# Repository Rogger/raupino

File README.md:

Raupino
=======
Raupino, an Arduino clone for DIY hobbiest

Detailed description: http://michaelrogger.wordpress.com/2014/03/23/raupino-an-arduino-clone/

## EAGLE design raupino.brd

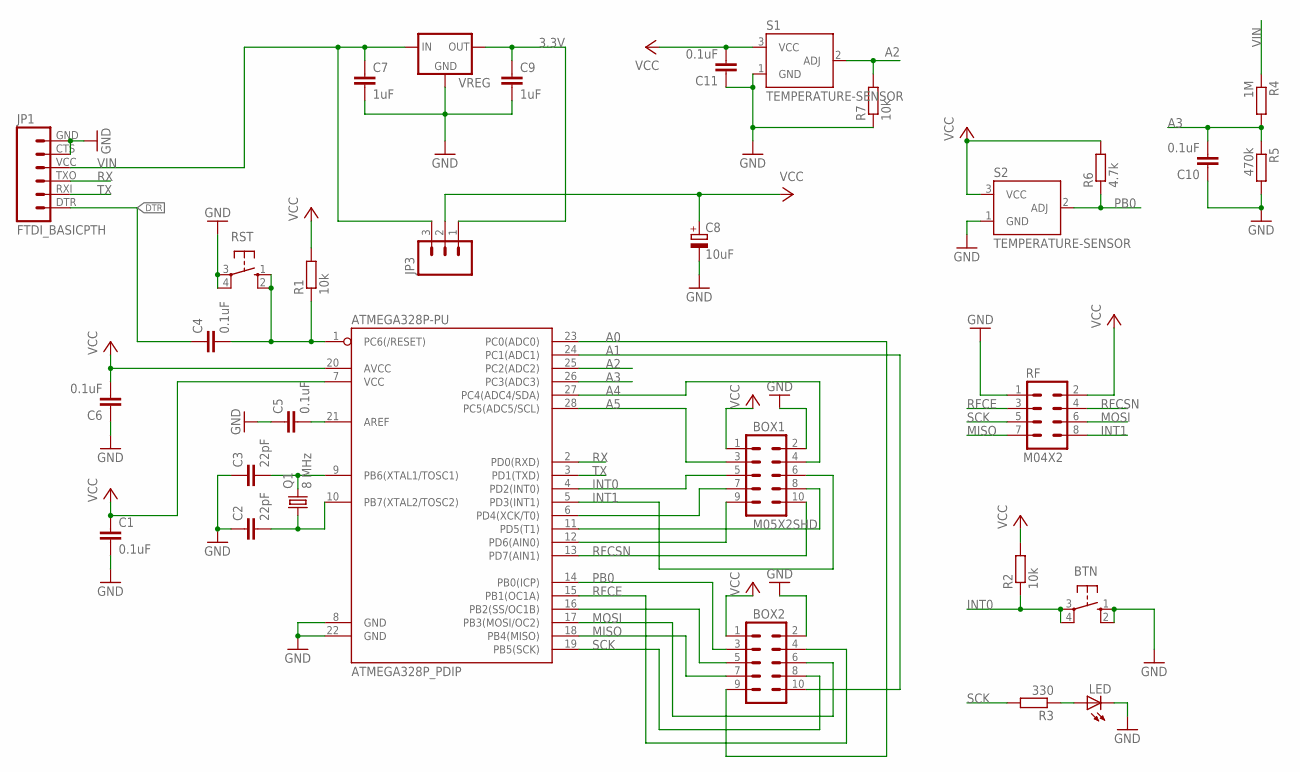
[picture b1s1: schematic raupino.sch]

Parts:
ATMEGA328P-PU: ATMEGA328P_PDIP; DIL28-3
BOX1, BOX2: M05X2SHD; 2X5-SHROUDED
BTN: 10-XX; B3F-10XX
C1, C4, C5, C6, C10, C11: 0.1uF; C0805
C2, C3: 22pF; C0805
C7, C9: 1uF; C050-025X075
C8: 10uF; TT2D5L
JP1: FTDI_BASICPTH; FTDI_BASIC
JP3: M03PTH; 1X03
LED: LED3MM
Q1: 8 MHz; HC49US
R1, R2, R7: 10k; R0805
R3: 330; R0805
R4: 1M; R0805
R5: 470k; R0805
R6: 4.7k; R0805
RF: M04X2; 2X4
RST: 10-XX; B3F-10XX
S1, S2: TEMPERATURE-SENSOR; TO-92
VREG: 78LXX

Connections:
3.3V: C9.1, JP3.1, VREG.OUT
A0: ATMEGA328P-PU.23 (PC0(ADC0)), BOX2.9
A1: ATMEGA328P-PU.24 (PC1(ADC1)), BOX2.10
A2: ATMEGA328P-PU.25 (PC2(ADC2)), R7.2, S1.2 (ADJ)
A3: ATMEGA328P-PU.26 (PC3(ADC3)), C10.2, R4.2, R5.1
A4: ATMEGA328P-PU.27 (PC4(ADC4/SDA)), BOX1.4
A5: ATMEGA328P-PU.28 (PC5(ADC5/SCL)), BOX1.3
DTR: C4.1, JP1.DTR (1)
GND: ATMEGA328P-PU.8 (GND), ATMEGA328P-PU.22 (GND), BOX1.2, BOX2.2, BTN.1 (S), BTN.2 (S1), C1.2, C2.1, C3.1, C5.1, C6.1, C7.2, C8.-, C9.2, C10.1, C11.1, JP1.CTS (5), JP1.GND (6), LED.K (C), R5.2, R7.1, RF.1, RST.3, RST.4 (P1), S1.1 (GND), S2.1 (GND), VREG.GND
INT0: ATMEGA328P-PU.4 (PD2(INT0)), BOX1.5, BTN.3, BTN.4 (P1), R2.1
INT1: ATMEGA328P-PU.5 (PD3(INT1)), BOX1.6, RF.8
MISO: ATMEGA328P-PU.18 (PB4(MISO)), BOX2.7, RF.7
MOSI: ATMEGA328P-PU.17 (PB3(MOSI/OC2)), BOX2.6, RF.6
unnamed: ATMEGA328P-PU.10 (PB7(XTAL2/TOSC2)), C2.2, Q1.1
unnamed: ATMEGA328P-PU.1 (PC6(/RESET)), C4.2, R1.1, RST.1 (S), RST.2 (S1)
unnamed: ATMEGA328P-PU.11 (PD5(T1)), BOX1.8
unnamed: ATMEGA328P-PU.9 (PB6(XTAL1/TOSC1)), C3.2, Q1.2
unnamed: ATMEGA328P-PU.12 (PD6(AIN0)), BOX1.9
unnamed: ATMEGA328P-PU.21 (AREF), C5.2
unnamed: LED.A, R3.1
unnamed: ATMEGA328P-PU.6 (PD4(XCK/T0)), BOX1.7
unnamed: ATMEGA328P-PU.16 (PB2(SS/OC1B)), BOX2.5
PB0: ATMEGA328P-PU.14 (PB0(ICP)), BOX2.3, R6.1, S2.2 (ADJ)
RFCE: ATMEGA328P-PU.15 (PB1(OC1A)), BOX2.4, RF.3
RFCSN: ATMEGA328P-PU.13 (PD7(AIN1)), BOX1.10, RF.4
RX: ATMEGA328P-PU.2 (PD0(RXD)), JP1.TXO (3)
SCK: ATMEGA328P-PU.19 (PB5(SCK)), BOX2.8, R3.2, RF.5
TX: ATMEGA328P-PU.3 (PD1(TXD)), JP1.RXI (2)
VCC: ATMEGA328P-PU.7 (VCC), ATMEGA328P-PU.20 (AVCC), BOX1.1, BOX2.1, C1.1, C6.2, C8.+, C11.2, JP3.2, R1.2, R2.2, R6.2, RF.2, S1.3 (VCC), S2.3 (VCC)
VIN: C7.1, JP1.VCC (4), JP3.3, R4.1, VREG.IN

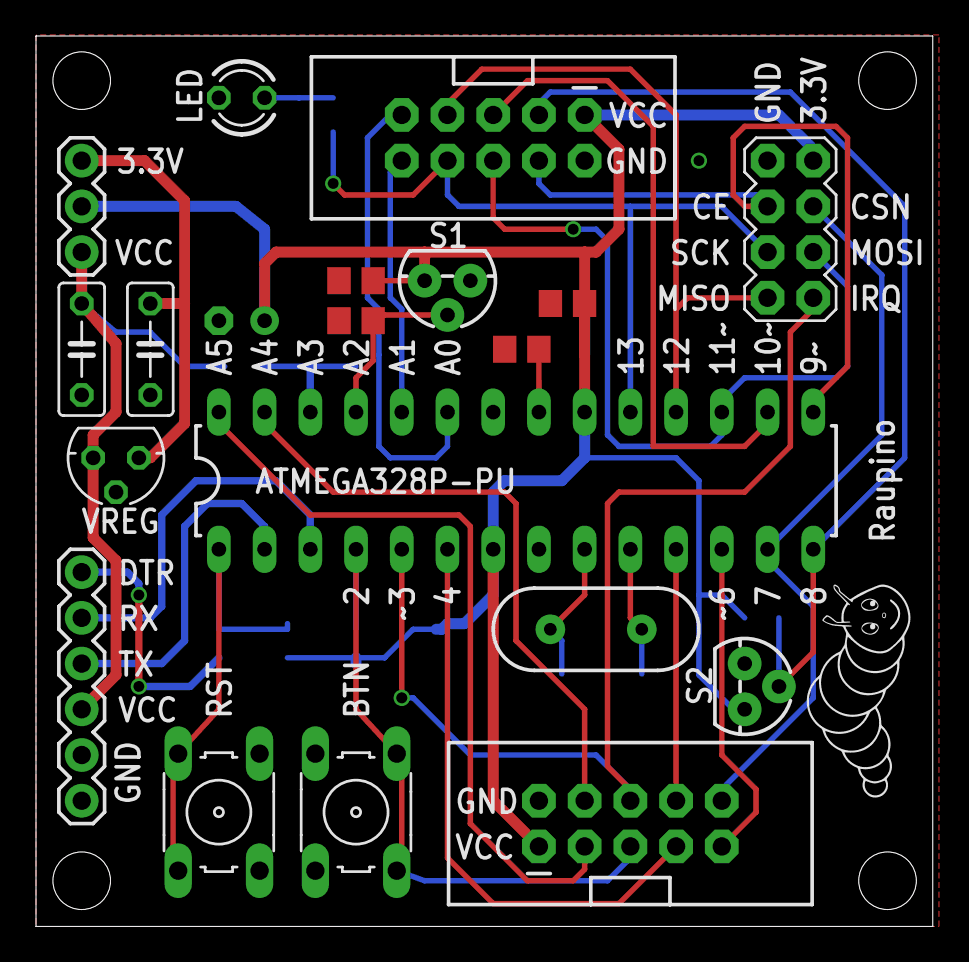
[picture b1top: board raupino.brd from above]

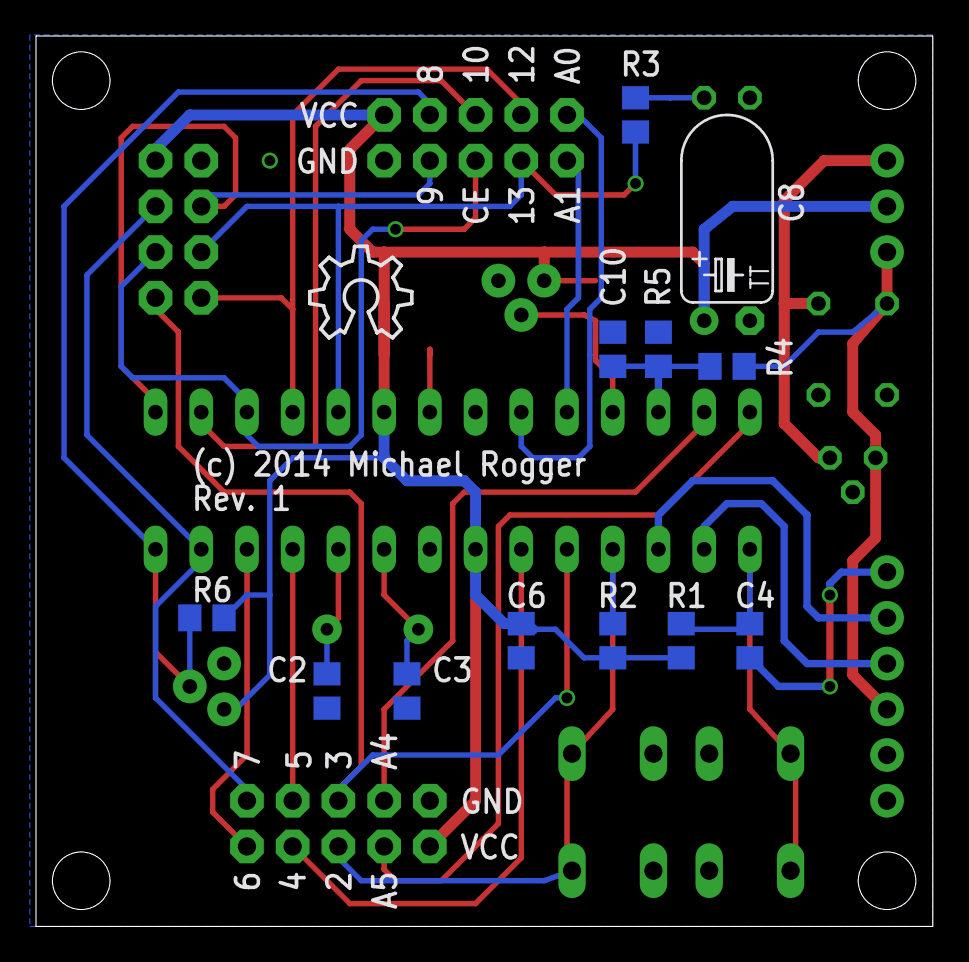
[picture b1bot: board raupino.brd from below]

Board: 2 copper layers, 49.8 x 49.5 mm, 32 parts (13 on the bottom side), 30 nets.

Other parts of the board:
U$1: OSHW_8X200_NOTEXT

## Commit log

2014-03-02 Raupino
2014-03-02 Added README and PDF's
2014-03-02 added gerber-view for top and bottom layer
2014-03-23 Updated URL in README
2014-03-23 Added schematic picture

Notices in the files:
raupino.brd:
(c) 2014 Michael Rogger
parts and their libraries:
SparkFun-DigitalIC: Licensing: CC v3.0 Share-Alike You are welcome to use this library for commercial purposes.
